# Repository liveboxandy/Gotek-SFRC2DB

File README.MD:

# Gotek-SFRC2DB
Initial schematic and gerbers for a Gotek SFRC2D.B based on an Artery St32F415 chip.
Used photographs and a multimeter without removing any chips. Only removed RA/RB/RC to verify connections to U3.
Should work for the STM105 variant as some of the smoothing caps don't make sense for the Artery but do for the STM.
Updated for Kicad 9.
Added ibom.
Restructured Folders

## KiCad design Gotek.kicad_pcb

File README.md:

# Gotek-SFRC2DB
Initial schematic and gerbers for a Gotek SFRC2D.B based on an Artery St32F415 chip.
Used photographs and a multimeter without removing any chips. Only removed RA/RB/RC to verify connections to U3.
Should work for the STM105 variant as some of the smoothing caps don't make sense for the Artery but do for the STM.
Updated for Kicad 9.
Added ibom.
Restructured Folders

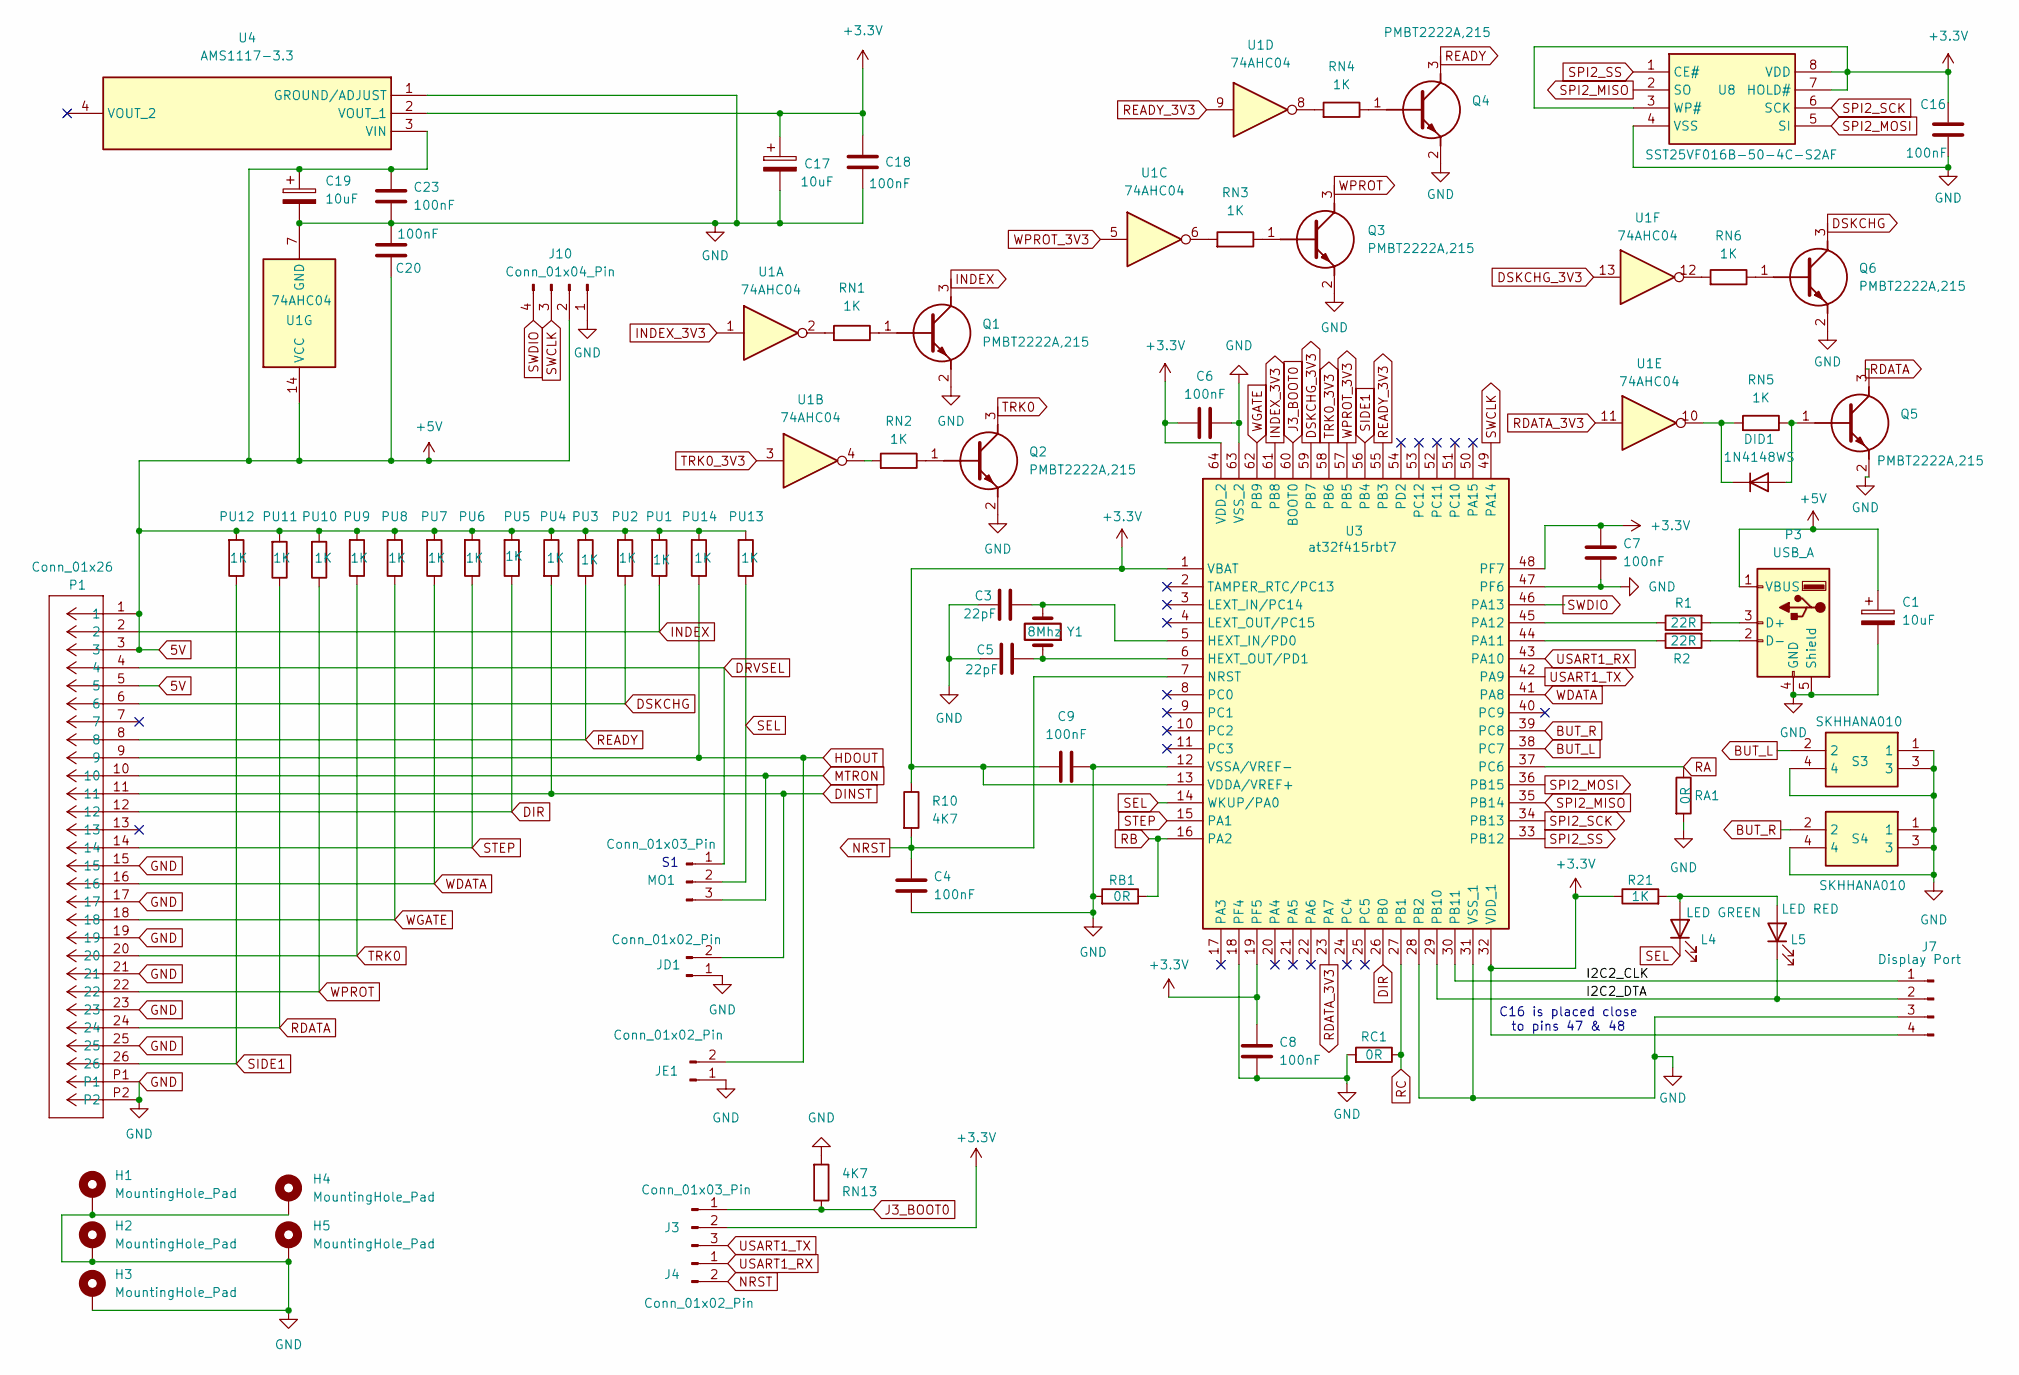
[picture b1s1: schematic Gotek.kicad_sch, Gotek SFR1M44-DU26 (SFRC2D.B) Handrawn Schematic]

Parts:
C1, C17, C19: 10uF; CP_Radial_D5.0mm_P2.50mm
C3, C5: 22pF; C_0805_2012Metric_Pad1.18x1.45mm_HandSolder
C4, C6, C7, C8, C9, C16, C18, C20, C23: 100nF; C_0805_2012Metric_Pad1.18x1.45mm_HandSolder
DID1: 1N4148WS; SODFL2512X90N
H1, H2, H3, H4, H5: MountingHole_Pad; MountingHole_M3_Pad
J3: Conn_01x03_Pin; PinHeader_1x03_P2.54mm_Vertical
J4: Conn_01x02_Pin; PinHeader_1x02_P2.54mm_Vertical
J7: Display Port; PinHeader_1x04_P2.54mm_Vertical
J10: Conn_01x04_Pin; PinHeader_1x04_P2.54mm_Vertical
JD1: Conn_01x02_Pin; PinHeader_1x02_P2.54mm_Horizontal
JE1: Conn_01x02_Pin; PinHeader_1x02_P2.54mm_Horizontal
L4: LED GREEN; LED_0805_2012Metric_Pad1.15x1.40mm_HandSolder
L5: LED RED; LED_0805_2012Metric_Pad1.15x1.40mm_HandSolder
MO1: Conn_01x03_Pin; PinHeader_1x03_P2.54mm_Horizontal
P1: Conn_01x26; MOLEX_CON_2005280260
P3: USB_A; USB_A_Molex_67643_Horizontal
PU1, PU2, PU3, PU4, PU5, PU6, PU7, PU8, PU9, PU10, PU11, PU12, PU13, PU14: 1K; R_0805_2012Metric_Pad1.20x1.40mm_HandSolder
Q1, Q2, Q3, Q4, Q5, Q6: PMBT2222A,215; SOT95P280X130-3N; Mouser Part Number 771-PMBT2222A-T/R
R1, R2: 22R; R_0805_2012Metric_Pad1.20x1.40mm_HandSolder
R10: 4K7; R_0805_2012Metric_Pad1.20x1.40mm_HandSolder
R21: 1K; R_0805_2012Metric_Pad1.20x1.40mm_HandSolder
RA1: 0R; R_0805_2012Metric_Pad1.20x1.40mm_HandSolder
RB1: 0R; R_0805_2012Metric_Pad1.20x1.40mm_HandSolder
RC1: 0R; R_0805_2012Metric_Pad1.20x1.40mm_HandSolder
RN1, RN2, RN3, RN4, RN5, RN6: 1K; R_0805_2012Metric_Pad1.20x1.40mm_HandSolder
RN13: 4K7; R_0805_2012Metric_Pad1.20x1.40mm_HandSolder
S3, S4: SKHHANA010; SKHHLQA010; Mouser Part Number 688-SKHHAN
U1: 74AHC04; SO-14_3.9x8.65mm_P1.27mm
U3: at32f415rbt7; QFP50P1200X1200X160-64N; Manufacturer_Part_Number at32f415rct7
U4: AMS1117-3.3; SOT229P700X180-4N; Manufacturer_Part_Number ams1117-3.3v
U8: SST25VF016B-50-4C-S2AF; SOIC127P790X216-8N; Mouser Part Number 579-25VF016B504CS2AF
Y1: 8Mhz; Crystal_HC18-U_Vertical

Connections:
5V: C1.1, C19.1, C20.2, C23.1, J10.2, P1.1, P1.3, P1.5, P3.1 (VBUS), PU1.2, PU2.2, PU3.2, PU4.1, PU5.2, PU6.2, PU7.2, PU8.2, PU9.2, PU10.2, PU11.2, PU12.2, PU13.2, PU14.2, U1.14 (VCC), U4.3 (VIN)
+3.3V: C6.1, C7.1, C8.1, C9.2, C16.2, C17.1, C18.2, J3.2, J7.4, R10.1, R21.1, U3.1 (VBAT), U3.13 (VDDA/VREF+), U3.19 (PF5), U3.32 (VDD_1), U3.48 (PF7), U3.64 (VDD_2), U4.2 (VOUT_1), U8.3 (WP#), U8.7 (HOLD#), U8.8 (VDD)
/I2C2_CLK: J7.1, U3.30 (PB11)
/I2C2_DTA: J7.2, L5.1 (K), U3.29 (PB10)
BUT_L: S3.2, U3.38 (PC7)
BUT_R: S4.2, U3.39 (PC8)
DINST: JD1.2, P1.11, PU4.2
DIR: P1.12, PU5.1, U3.26 (PB0)
DRVSEL: MO1.1, P1.4
DSKCHG: P1.6, PU2.1, Q6.3 (C)
DSKCHG_3V3: U1.13, U3.59 (PB7)
GND: C1.2, C3.1, C4.2, C5.2, C6.2, C7.2, C8.2, C9.1, C16.1, C17.2, C18.1, C19.2, C20.1, C23.2, H1.1, H2.1, H3.1, H4.1, H5.1, J7.3, J10.1, JD1.1, JE1.1, P1.15, P1.17, P1.19, P1.21, P1.23, P1.25, P1.P1, P1.P2, P3.4 (GND), P3.5 (Shield), Q1.2 (E), Q2.2 (E), Q3.2 (E), Q4.2 (E), Q5.2 (E), Q6.2 (E), RA1.2, RB1.2, RC1.2, RN13.2, S3.1, S3.3, S3.4, S4.1, S4.3, S4.4, U1.7 (GND), U3.12 (VSSA/VREF-), U3.18 (PF4), U3.28 (PB2), U3.31 (VSS_1), U3.47 (PF6), U3.63 (VSS_2), U4.1 (GROUND/ADJUST), U8.4 (VSS)
HDOUT: JE1.2, P1.9, PU14.1
INDEX: P1.2, PU1.1, Q1.3 (C)
INDEX_3V3: U1.1, U3.61 (PB8)
J3_BOOT0: J3.1, RN13.1, U3.60 (BOOT0)
MTRON: MO1.3, P1.10
NRST: C4.1, J4.2, R10.2, U3.7 (NRST)
unnamed: DID1.2 (A), Q5.1 (B), RN5.1
unnamed: DID1.1 (K), RN5.2, U1.10
unnamed: L4.2 (A), L5.2 (A), R21.2
unnamed: P3.3 (D+), R1.2
unnamed: P3.2 (D-), R2.2
unnamed: Q1.1 (B), RN1.1
unnamed: Q2.1 (B), RN2.1
unnamed: Q3.1 (B), RN3.1
unnamed: Q4.1 (B), RN4.1
unnamed: Q6.1 (B), RN6.1
unnamed: RN1.2, U1.2
unnamed: RN2.2, U1.4
unnamed: RN3.2, U1.6
unnamed: RN4.2, U1.8
unnamed: RN6.2, U1.12
unnamed: C3.2, U3.5 (HEXT_IN/PD0), Y1.2
unnamed: C5.1, U3.6 (HEXT_OUT/PD1), Y1.1
unnamed: R2.1, U3.44 (PA11)
unnamed: R1.1, U3.45 (PA12)
RA: RA1.1, U3.37 (PC6)
RB: RB1.1, U3.16 (PA2)
RC: RC1.1, U3.27 (PB1)
RDATA: P1.24, PU11.1, Q5.3 (C)
RDATA_3V3: U1.11, U3.23 (PA7)
READY: P1.8, PU3.1, Q4.3 (C)
READY_3V3: U1.9, U3.55 (PB3)
SEL: L4.1 (K), MO1.2, PU13.1, U3.14 (WKUP/PA0)
SIDE1: P1.26, PU12.1, U3.56 (PB4)
SPI2_MISO: U3.35 (PB14), U8.2 (SO)
SPI2_MOSI: U3.36 (PB15), U8.5 (SI)
SPI2_SCK: U3.34 (PB13), U8.6 (SCK)
SPI2_SS: U3.33 (PB12), U8.1 (CE#)
STEP: P1.14, PU6.1, U3.15 (PA1)
SWCLK: J10.3, U3.49 (PA14)
SWDIO: J10.4, U3.46 (PA13)
TRK0: P1.20, PU9.1, Q2.3 (C)
TRK0_3V3: U1.3, U3.58 (PB6)
USART1_RX: J4.1, U3.43 (PA10)
USART1_TX: J3.3, U3.42 (PA9)
WDATA: P1.16, PU7.1, U3.41 (PA8)
WGATE: P1.18, PU8.1, U3.62 (PB9)
WPROT: P1.22, PU10.1, Q3.3 (C)
WPROT_3V3: U1.5, U3.57 (PB5)

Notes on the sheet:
C16 is placed close to pins 47 & 48

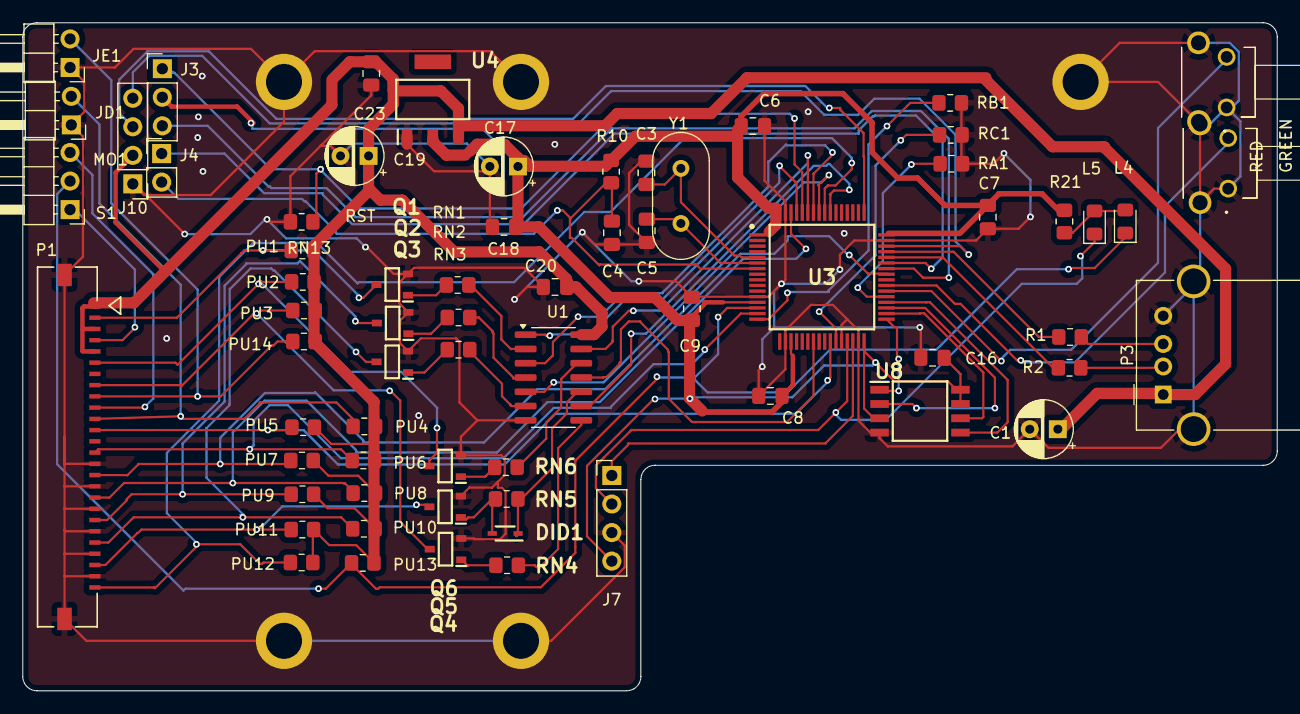
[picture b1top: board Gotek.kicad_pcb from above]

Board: 2 copper layers, 111.6 x 59.4 mm, 72 parts (0 on the bottom side), 61 nets.

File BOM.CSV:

"Reference","Value","Datasheet","Footprint","Qty","DNP"
"C1,C17,C19","10uF","~","Capacitor_THT:CP_Radial_D5.0mm_P2.50mm","3",""
"C3,C5","22pF","~","Capacitor_SMD:C_0805_2012Metric_Pad1.18x1.45mm_HandSolder","2",""
"C4,C6,C7,C8,C9,C16,C18,C20,C23","100nF","~","Capacitor_SMD:C_0805_2012Metric_Pad1.18x1.45mm_HandSolder","9",""
"DID1","1N4148WS","https://www.vishay.com/docs/85751/1n4148ws.pdf","Gotek:SODFL2512X90N","1",""
"J3,MO1","Conn_01x03_Pin","~","Connector_PinHeader_2.54mm:PinHeader_1x03_P2.54mm_Horizontal,Connector_PinHeader_2.54mm:PinHeader_1x03_P2.54mm_Vertical","2",""
"J4,JD1,JE1","Conn_01x02_Pin","~","Connector_PinHeader_2.54mm:PinHeader_1x02_P2.54mm_Horizontal,Connector_PinHeader_2.54mm:PinHeader_1x02_P2.54mm_Vertical","3",""
"J7","Display Port","~","Connector_PinHeader_2.54mm:PinHeader_1x04_P2.54mm_Vertical","1",""
"J10","Conn_01x04_Pin","~","Connector_PinHeader_2.54mm:PinHeader_1x04_P2.54mm_Vertical","1",""
"L4","LED GREEN","~","LED_SMD:LED_0805_2012Metric_Pad1.15x1.40mm_HandSolder","1",""
"L5","LED RED","~","LED_SMD:LED_0805_2012Metric_Pad1.15x1.40mm_HandSolder","1",""
"P1","Conn_01x26","2005280260","Gotek:MOLEX_CON_2005280260","1",""
"P3","USB_A","~","Connector_USB:USB_A_Molex_67643_Horizontal","1",""
"PU1,PU2,PU3,PU4,PU5,PU6,PU7,PU8,PU9,PU10,PU11,PU12,PU13,PU14,R21,RN1,RN2,RN3,RN4,RN5,RN6","1K","~","Resistor_SMD:R_0805_2012Metric_Pad1.20x1.40mm_HandSolder","21",""
"Q1,Q2,Q3,Q4,Q5,Q6","PMBT2222A,215","https://assets.nexperia.com/documents/data-sheet/PMBT2222A.pdf","Gotek:SOT95P280X130-3N","6",""
"R1,R2","22R","~","Resistor_SMD:R_0805_2012Metric_Pad1.20x1.40mm_HandSolder","2",""
"R10,RN13","4K7","~","Resistor_SMD:R_0805_2012Metric_Pad1.20x1.40mm_HandSolder","2",""
"RA1,RB1,RC1","0R","~","Resistor_SMD:R_0805_2012Metric_Pad1.20x1.40mm_HandSolder","3",""
"S3,S4","SKHHANA010","https://www.mouser.co.uk/datasheet/2/15/SKHH-1370651.pdf","Gotek:SKHHLQA010","2",""
"U1","74AHC04","https://assets.nexperia.com/documents/data-sheet/74AHC_AHCT04.pdf","Package_SO:SO-14_3.9x8.65mm_P1.27mm","1",""
"U3","at32f415rbt7","https://www.arterytek.com/download/DS/DS_AT32F415_V2.01_CH.pdf","Gotek:QFP50P1200X1200X160-64N","1",""
"U4","AMS1117-3.3","http://www.advanced-monolithic.com/pdf/ds1117.pdf","Gotek:SOT229P700X180-4N","1",""
"U8","SST25VF016B-50-4C-S2AF","https://ww1.microchip.com/downloads/en/DeviceDoc/20005044C.pdf","Gotek:SOIC127P790X216-8N","1",""
"Y1","8Mhz","~","Crystal:Crystal_HC18-U_Vertical","1",""

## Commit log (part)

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2024-10-09 Add files via upload
    Updated to correct schematic positioning of C7 and C16. Layout did not change.
2024-10-10 Add files via upload
    Corrected values for R10 and RN13 (4K7).
2025-10-22 Updated for Kicad9. Added ibom.
    Updated for Kicad 9
    Added ibom.
    Restructured folders
